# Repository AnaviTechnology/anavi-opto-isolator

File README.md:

# ANAVI Opto-isolator

Open source hardware printed circuit board for Arduino, ESP32, ESP8266, Raspberry Pi, etc. Supports 12V to 3.3V, 12V to 5V, 24V to 3.3V, 24V to 5V.

# License

The project is released under the [Creative Commons Attribution-ShareAlike 4.0 International (CC BY-SA 4.0)](https://creativecommons.org/licenses/by-sa/4.0/).

Note: This is a human-readable summary of (and not a substitute for) the [license](https://creativecommons.org/licenses/by-sa/4.0/legalcode).

You are free to:

Share — copy and redistribute the material in any medium or format Adapt — remix, transform, and build upon the material for any purpose, even commercially. The licensor cannot revoke these freedoms as long as you follow the license terms. Under the following terms:

Attribution — You must give appropriate credit, provide a link to the license, and indicate if changes were made. You may do so in any reasonable manner, but not in any way that suggests the licensor endorses you or your use. ShareAlike — If you remix, transform, or build upon the material, you must distribute your contributions under the same license as the original. No additional restrictions — You may not apply legal terms or technological measures that legally restrict others from doing anything the license permits. Notices:

You do not have to comply with the license for elements of the material in the public domain or where your use is permitted by an applicable exception or limitation. No warranties are given. The license may not give you all of the permissions necessary for your intended use. For example, other rights such as publicity, privacy, or moral rights may limit how you use the material.

You will have to provide a link to the original creator of the project http://www.anavi.technology on any documentation or website.

Credit can be attributed through a link to the creator website: http://www.anavi.technology

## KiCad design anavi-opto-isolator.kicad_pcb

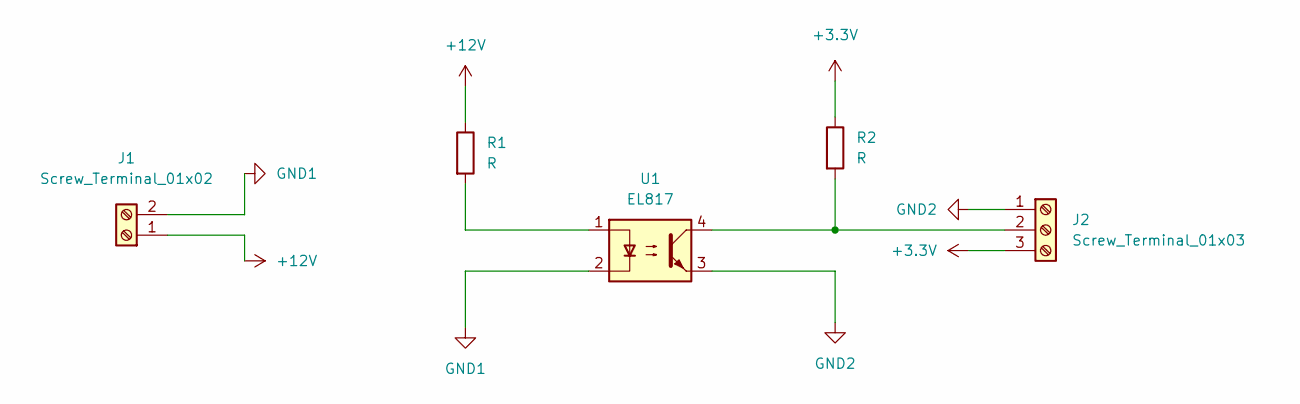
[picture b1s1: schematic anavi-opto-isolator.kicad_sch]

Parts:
J1: Screw_Terminal_01x02; TerminalBlock_Phoenix_MKDS-1,5-2_1x02_P5.00mm_Horizontal
J2: Screw_Terminal_01x03; TerminalBlock_Phoenix_MKDS-1,5-3_1x03_P5.00mm_Horizontal
R1, R2: R; R_0805_2012Metric_Pad1.20x1.40mm_HandSolder
U1: EL817; EL817S_EVE

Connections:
+3V3: J2.3, R2.1
+12V: J1.1, R1.1
GND1: J1.2, U1.2
GND2: J2.1, U1.3
unnamed: J2.2, R2.2, U1.4
unnamed: R1.2, U1.1

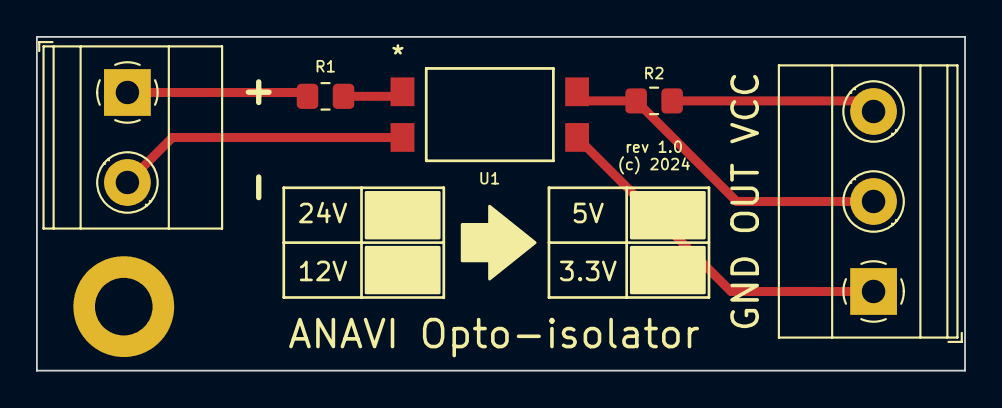
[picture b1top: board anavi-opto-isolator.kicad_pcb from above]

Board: 2 copper layers, 51.6 x 18.5 mm, 6 parts (0 on the bottom side), 6 nets.

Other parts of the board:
REF1: MountingHole_3.2mm_M3_DIN965_Pad

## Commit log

2024-06-02 Initial commit
    Opto-isolator board that supports:
    12V -> 3.3V
    12V -> 5V
    24V -> 3.3V
    24V -> 5V
2024-06-02 anavi-opto-isolator: Add text on the back
    Add text about open source hardware on the back of the printed
    circuit board.

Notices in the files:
anavi-opto-isolator.kicad_pcb:
(c) 2024
